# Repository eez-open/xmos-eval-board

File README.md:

### Ownership and License

The contributors are listed in CONTRIB.TXT. This project uses the TAPR v1.0 license, see LICENSE.TXT.
EEZ _xmos-eval-board_ uses the [C4.1 (Collective Code Construction Contract)](http://rfc.zeromq.org/spec:22) process for contributions.
To report an issue, use the [issue tracker](https://github.com/eez-open/xmos-eval-board/issues).

### Overview

This project is an attempt to learn more about [XMOS xCORE-200](http://www.xmos.com/products/silicon/xcore-200) multicore microcontroller XE216-512-TQ128 by making evaluation board that would be used as a prototype or building block in some future DIY open source Test & Measurement (T&M) projects.
Selected MCU has 16 _logical_ cores divided between two hardware cores (_tiles_)and include USB 2.0 and [RGMII](https://en.wikipedia.org/wiki/Media-independent_interface) for Gigabit Ethernet. It has the highest pin count that comes in easy to mounting package (not BGA).
The evaluation board is based on XMOS evaluation boards and a couple of so-called _sliceCARDs_.

Evaluation board features:

- PCB dimension: 100 x 85 mm
- Power supply: 12 Vdc with on board regulators for 1 V, 3.3 V (sequenced) and 5 V (for USB host)
- XSYS 20-pin IDC connector for JTAG and real-time debugging (via 2-wire _xlink0_) with ESD protection
- USB AB-mini 5-pin plug with ESD protection (hopefully can be used for [OTG](https://en.wikipedia.org/wiki/USB_On-The-Go) operation)
- Support for RGB 4.3" LCD TFT (40-pin FFC 0.5 mm), 16-bit color space supported
- LCD WLED power supply with brightness control (PWM)
- Resistive touch screen controller (SPI)
- QSPI Flash memory
- 10-pin IDC connector for direct access to Flash memory
- 16-bit I/O port expander with 2 opto-isolated input, 2 opto-isolated outputs, 3 on-board LEDs, 3 TVS protected inputs
- Real time clock (SPI) with supercap backup (Vbat)
- EEPROM (SPI)
- SDRAM (multiplexed address and data bus)
- 20-pin FFC 0.5 mm socket for Riverdi LCD TFT displays (SPI, Audio out)
- Micro SD Card socket (SPI)
- 10/100 Mbit Ethernet PHY with RJ-45 socket
- Low-power audio amplifier
- 10-pin header for cheap W5500 Ethernet module (SPI)
- Reset switch

For MCU pin mapping check _[Portmap for EEZ evaluation board](XE216-512-TQ128_portmap_for_EEZ_evaluation_board_r1B4.pdf)_

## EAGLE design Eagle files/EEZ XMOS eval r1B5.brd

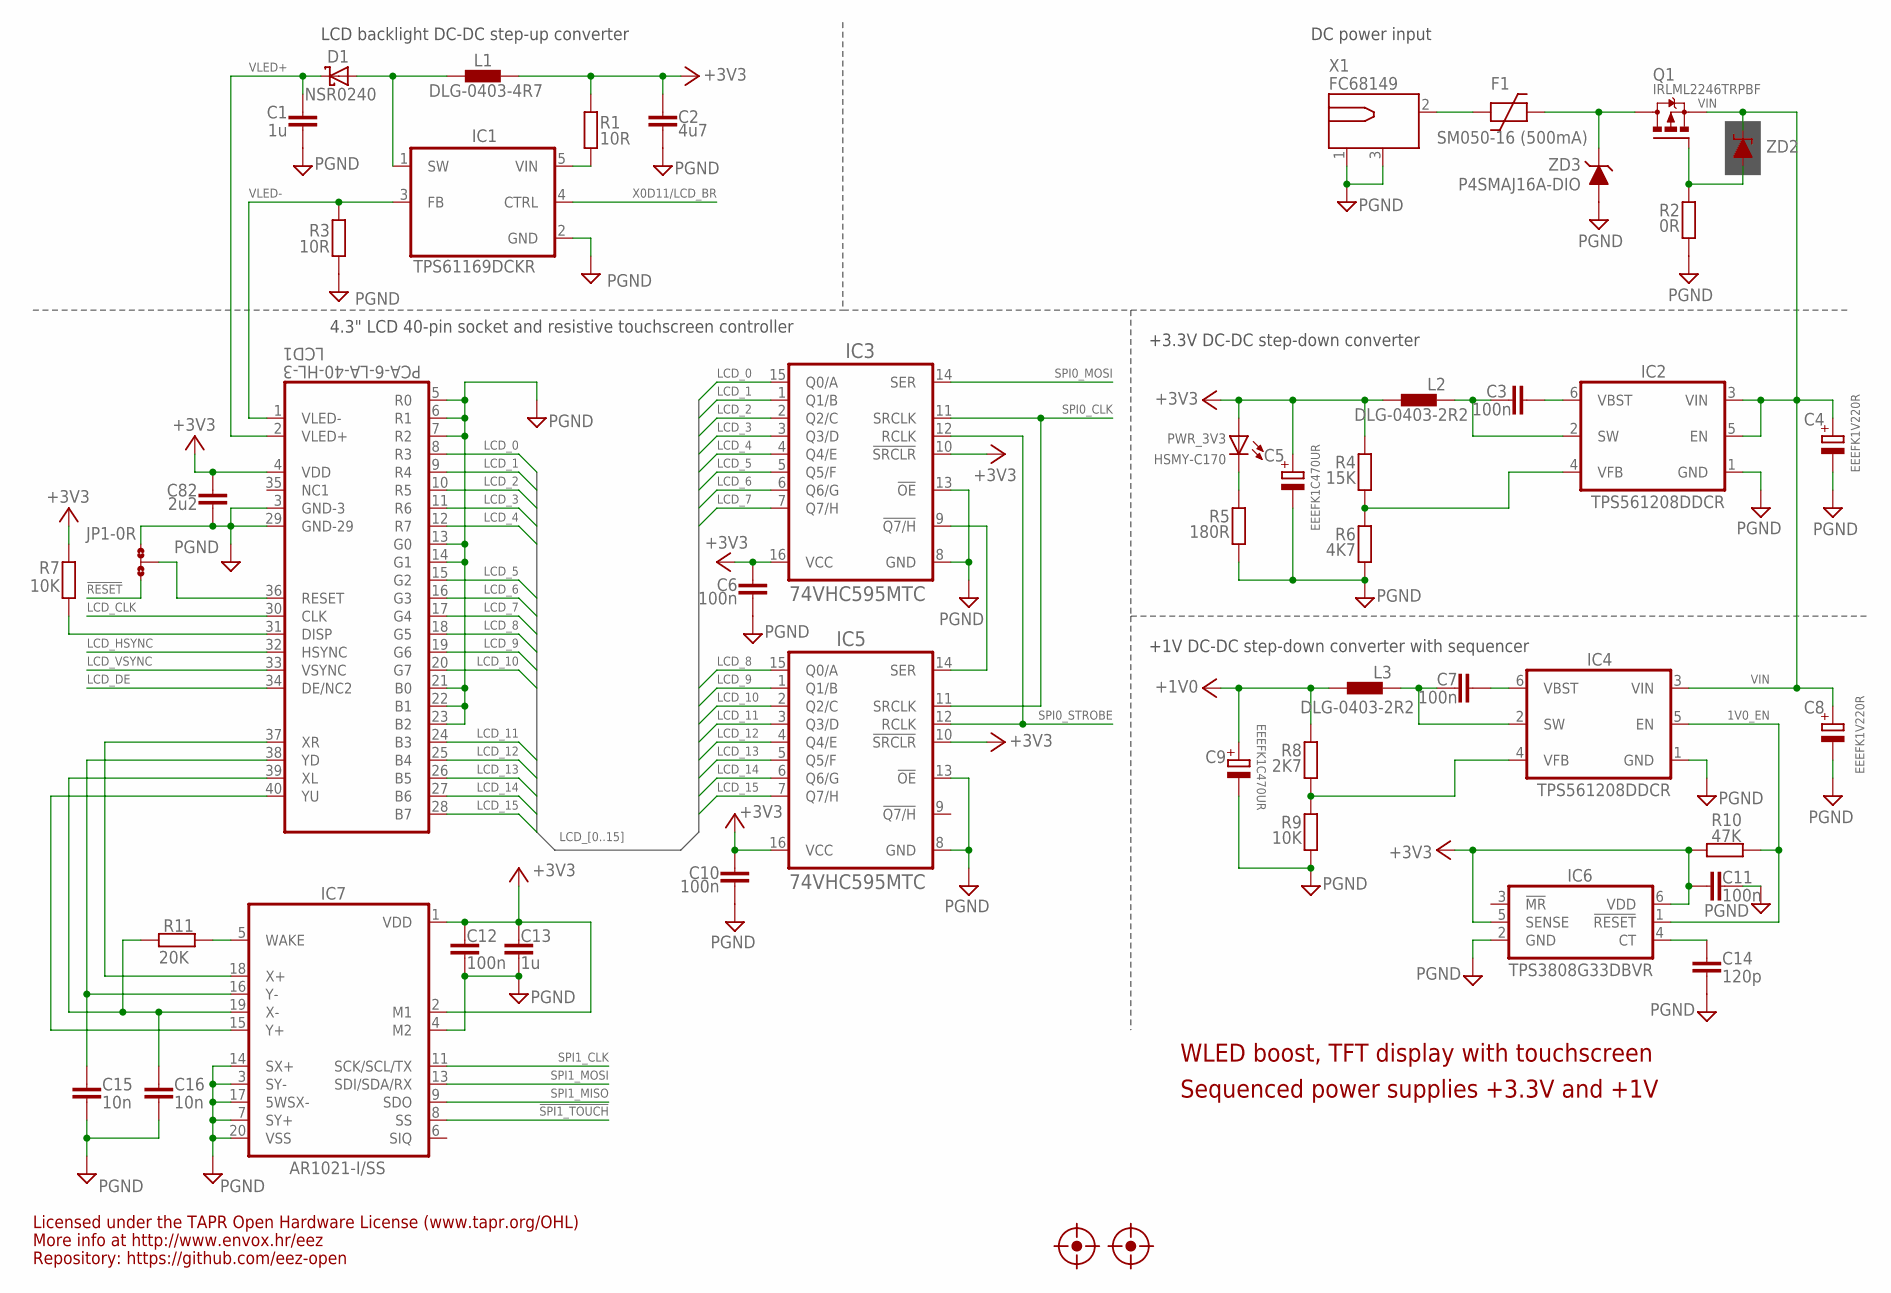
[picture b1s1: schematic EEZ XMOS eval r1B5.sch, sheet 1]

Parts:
C1, C13: 1u; C0805
C2: 4u7; C1206
C3, C6, C7, C10, C11, C12: 100n; C0603
C4: EEEFK1V220R; CAPAE530X610N
C5, C9: EEEFK1C470UR; CAPAE530X610N; TOLERANCE ±20 %; VOLTAGERATING 35V; MPN EEE-FK1V100R
C8: EEEFK1V220R; CAPAE530X610N; TOLERANCE ±20 %; VOLTAGERATING 35V; MPN EEE-FK1V100R
C14: 120p; C0805
C15, C16: 10n; C0805
C82: 2u2; C0805
D1: NSR0240; SOD123
F1: SM050-16 (500mA); F1210
FM1, FM2: FIDUCIAL_2; FIDUCIAL_DUAL
IC1: TPS61169DCKR; DCK0005A_N
IC2, IC4: TPS561208DDCR; DBV6
IC3, IC5: 74VHC595MTC; PW(R-PDSO-G16)
IC6: TPS3808G33DBVR; DBV6
IC7: AR1021-I/SS; SOP65P780X200-20N
JP1: 0R-JUMPA; A0R-JMP
L1: DLG-0403-4R7; DE0403
L2, L3: DLG-0403-2R2; DE0403
LCD1: PCA-6-LA-40-HL-3; FPC_40
PWR_3V3: HSMY-C170; LED_0805
Q1: IRLML2246TRPBF; SOT95P237X112-3N
R1, R3: 10R; R1206
R2: 0R; R0805
R4: 15K; R0805
R5: 180R; R0805
R6: 4K7; R0805
R7, R9: 10K; R0805
R8: 2K7; R0805
R10: 47K; R0805
R11: 20K; R0805
X1: FC68149; DC-21MM
ZD2: ZENER-DIODESOD323; SOD323-W
ZD3: P4SMAJ16A-DIO; DO214AC

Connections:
1V0_EN: IC4.5 (EN), IC6.1 (!RESET), R10.1
!RESET: JP1.1; also elsewhere on the board
!SPI1_TOUCH: IC7.8 (SS); also elsewhere on the board
+1V0: C9.1, L3.2, R8.2; also elsewhere on the board
+1V0_SW: C7.1, IC4.2 (SW), L3.1
+3V3: C2.1, C5.1, C6.2, C10.2, C11.2, C12.2, C13.2, C82.1, IC3.10 (!SRCLR), IC3.16 (VCC), IC5.10 (!SRCLR), IC5.16 (VCC), IC6.5 (SENSE), IC6.6 (VDD), IC7.1 (VDD), IC7.2 (M1), L1.1, L2.2, LCD1.4 (VDD), PWR_3V3.A, R1.1, R4.2, R7.2, R10.2; also elsewhere on the board
+3V3_SW: C3.1, IC2.2 (SW), L2.1
GND: C1.2, C2.2, C4.2, C5.2, C6.1, C8.2, C9.2, C10.1, C11.1, C12.1, C13.1, C14.2, C15.2, C16.2, C82.2, IC1.2 (GND), IC2.1 (GND), IC3.8 (GND), IC3.13 (!OE), IC4.1 (GND), IC5.8 (GND), IC5.13 (!OE), IC6.2 (GND), IC7.3 (SY-), IC7.4 (M2), IC7.7 (SY+), IC7.14 (SX+), IC7.17 (5WSX-), IC7.20 (VSS), JP1.3, LCD1.3 (GND-3), LCD1.5 (R0), LCD1.6 (R1), LCD1.7 (R2), LCD1.13 (G0), LCD1.14 (G1), LCD1.21 (B0), LCD1.22 (B1), LCD1.23 (B2), LCD1.29 (GND-29), R2.1, R3.2, R5.1, R6.1, R9.1, X1.1, X1.3, ZD3.A; also elsewhere on the board
LCD_0: IC3.15 (Q0/A), LCD1.8 (R3)
LCD_1: IC3.1 (Q1/B), LCD1.9 (R4)
LCD_2: IC3.2 (Q2/C), LCD1.10 (R5)
LCD_3: IC3.3 (Q3/D), LCD1.11 (R6)
LCD_4: IC3.4 (Q4/E), LCD1.12 (R7)
LCD_5: IC3.5 (Q5/F), LCD1.15 (G2)
LCD_6: IC3.6 (Q6/G), LCD1.16 (G3)
LCD_7: IC3.7 (Q7/H), LCD1.17 (G4)
LCD_8: IC5.15 (Q0/A), LCD1.18 (G5)
LCD_9: IC5.1 (Q1/B), LCD1.19 (G6)
LCD_10: IC5.2 (Q2/C), LCD1.20 (G7)
LCD_11: IC5.3 (Q3/D), LCD1.24 (B3)
LCD_12: IC5.4 (Q4/E), LCD1.25 (B4)
LCD_13: IC5.5 (Q5/F), LCD1.26 (B5)
LCD_14: IC5.6 (Q6/G), LCD1.27 (B6)
LCD_15: IC5.7 (Q7/H), LCD1.28 (B7)
LCD_CLK: LCD1.30 (CLK); also elsewhere on the board
LCD_DE: LCD1.34 (DE/NC2); also elsewhere on the board
LCD_HSYNC: LCD1.32 (HSYNC); also elsewhere on the board
LCD_VSYNC: LCD1.33 (VSYNC); also elsewhere on the board
unnamed: PWR_3V3.C, R5.2
unnamed: IC7.15 (Y+), LCD1.40 (YU)
unnamed: C16.1, IC7.19 (X-), LCD1.39 (XL), R11.2
unnamed: IC7.18 (X+), LCD1.37 (XR)
unnamed: Q1.1 (G), R2.2, ZD2.A
unnamed: IC7.5 (WAKE), R11.1
unnamed: F1.1, X1.2
unnamed: JP1.2, LCD1.36 (RESET)
unnamed: IC2.4 (VFB), R4.1, R6.2
unnamed: IC1.5 (VIN), R1.2
unnamed: C3.2, IC2.6 (VBST)
unnamed: IC3.9 (!Q7/H), IC5.14 (SER)
unnamed: IC4.4 (VFB), R8.1, R9.2
unnamed: C7.2, IC4.6 (VBST)
unnamed: C15.1, IC7.16 (Y-), LCD1.38 (YD)
unnamed: C14.1, IC6.4 (CT)
unnamed: LCD1.31 (DISP), R7.1
PMOS_D: F1.2, Q1.3 (D), ZD3.C
SPI0_CLK: IC3.11 (SRCLK), IC5.11 (SRCLK); also elsewhere on the board
SPI0_MOSI: IC3.14 (SER); also elsewhere on the board
SPI0_STROBE: IC3.12 (RCLK), IC5.12 (RCLK); also elsewhere on the board
SPI1_CLK: IC7.11 (SCK/SCL/TX); also elsewhere on the board
SPI1_MISO: IC7.9 (SDO); also elsewhere on the board
SPI1_MOSI: IC7.13 (SDI/SDA/RX); also elsewhere on the board
SW_WLED: D1.A, IC1.1 (SW), L1.2
VIN: C4.1, C8.1, IC2.3 (VIN), IC2.5 (EN), IC4.3 (VIN), Q1.2 (S), ZD2.C; also elsewhere on the board
VLED+: C1.1, D1.C, LCD1.2 (VLED+)
VLED-: IC1.3 (FB), LCD1.1 (VLED-), R3.1
X0D11/LCD_BR: IC1.4 (CTRL); also elsewhere on the board

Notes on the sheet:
Licensed under the TAPR Open Hardware License (www.tapr.org/OHL)
Repository: https://github.com/eez-open
More info at http://www.envox.hr/eez
Sequenced power supplies +3.3V and +1V
4.3" LCD 40-pin socket and resistive touchscreen controller
LCD backlight DC-DC step-up converter
WLED boost, TFT display with touchscreen
DC power input
+3.3V DC-DC step-down converter
+1V DC-DC step-down converter with sequencer

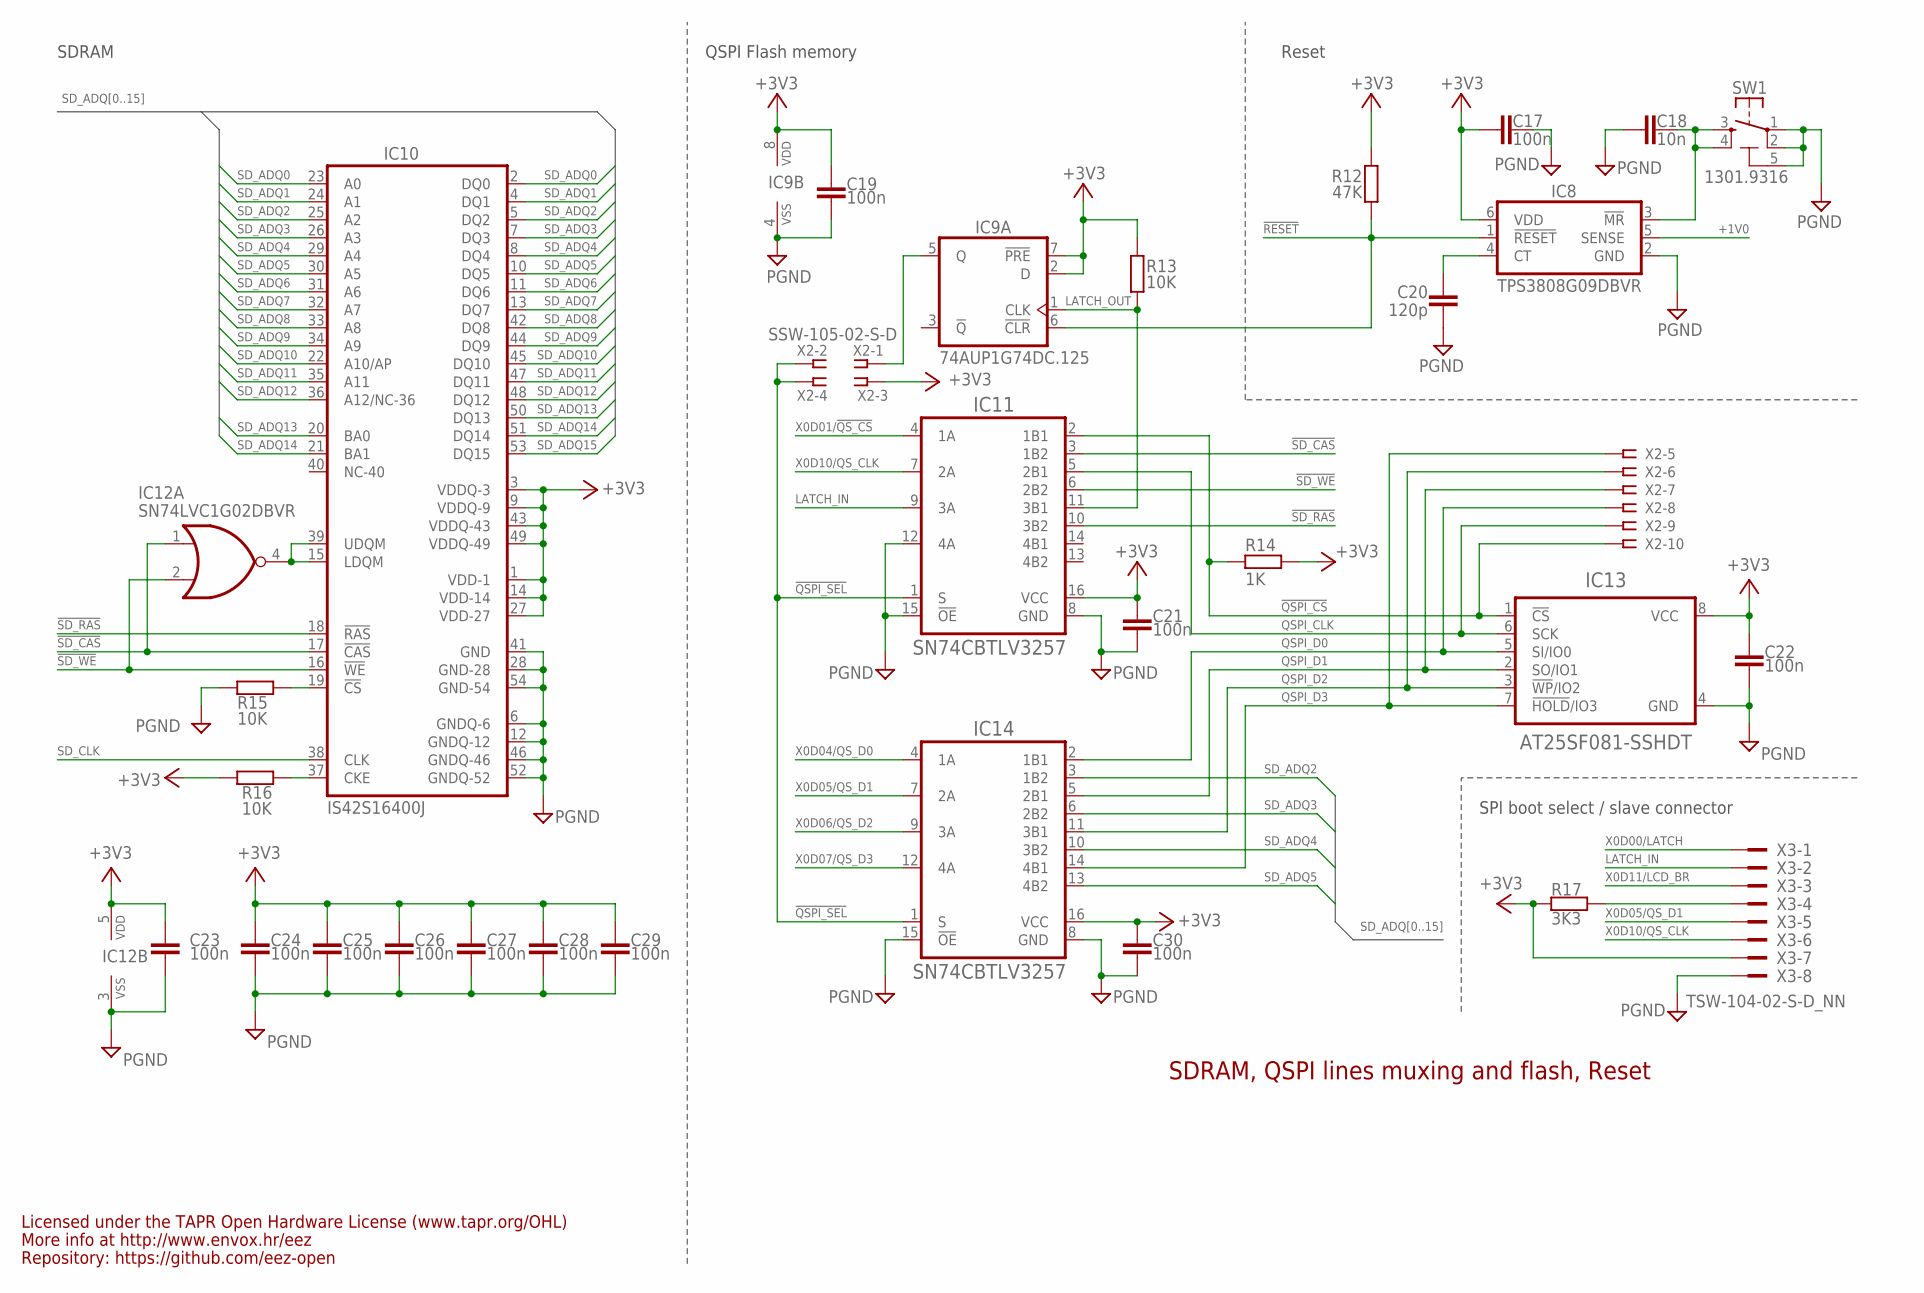
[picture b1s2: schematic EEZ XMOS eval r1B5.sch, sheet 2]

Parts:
C17, C19, C21, C22, C23, C24, C25, C26, C27, C28, C29, C30: 100n; C0603
C18: 10n; C0805
C20: 120p; C0805
IC8: TPS3808G09DBVR; DBV6; MANUFACTURER_PART_NUMBER tps3808g01_dbv_6
IC9: 74AUP1G74DC.125; DCU8
IC10: IS42S16400J; TSOPII-54
IC11, IC14: SN74CBTLV3257; PW(R-PDSO-G16)
IC12: SN74LVC1G02DBVR; DBV5
IC13: AT25SF081-SSHDT; SOIC127P600X175-8N
R12: 47K; R0805
R13, R15, R16: 10K; R0805
R14: 1K; R0805
R17: 3K3; R0805
SW1: 1301.9316; TACTM-6XN
X2: SSW-105-02-S-D
X3: TSW-104-02-S-D_NN; TSW-104-02-S-D-NONUM

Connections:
!QSPI_CS: IC11.2 (1B1), IC13.1 (!CS), R14.2, X2.10
!QSPI_SEL: IC11.1 (S), IC14.1 (S), X2.2, X2.4
!RESET: IC8.1 (!RESET), IC9.6 (!CLR), R12.2; also elsewhere on the board
!SD_CAS: IC10.17 (!CAS), IC11.3 (1B2), IC12.1 (A)
!SD_RAS: IC10.18 (!RAS), IC11.10 (3B2)
!SD_WE: IC10.16 (!WE), IC11.6 (2B2), IC12.2 (B)
+1V0: IC8.5 (SENSE); also elsewhere on the board
+3V3: C17.1, C19.1, C21.1, C22.1, C23.1, C24.1, C25.1, C26.1, C27.1, C28.1, C29.1, C30.1, IC8.6 (VDD), IC9.2 (D), IC9.7 (!PRE), IC9.8 (VDD), IC10.1 (VDD-1), IC10.3 (VDDQ-3), IC10.9 (VDDQ-9), IC10.14 (VDD-14), IC10.27 (VDD-27), IC10.43 (VDDQ-43), IC10.49 (VDDQ-49), IC11.16 (VCC), IC12.5 (VDD), IC13.8 (VCC), IC14.16 (VCC), R12.1, R13.1, R14.1, R16.2, R17.2, X2.3, X3.7; also elsewhere on the board
GND: C17.2, C18.1, C19.2, C20.2, C21.2, C22.2, C23.2, C24.2, C25.2, C26.2, C27.2, C28.2, C29.2, C30.2, IC8.2 (GND), IC9.4 (VSS), IC10.6 (GNDQ-6), IC10.12 (GNDQ-12), IC10.28 (GND-28), IC10.41 (GND), IC10.46 (GNDQ-46), IC10.52 (GNDQ-52), IC10.54 (GND-54), IC11.8 (GND), IC11.12 (4A), IC11.15 (!OE), IC12.3 (VSS), IC13.4 (GND), IC14.8 (GND), IC14.15 (!OE), R15.2, SW1.1, SW1.2, SW1.5 (5-GND), X3.8; also elsewhere on the board
LATCH_IN: IC11.9 (3A), X3.2
LATCH_OUT: IC9.1 (CLK), IC11.11 (3B1), R13.2
unnamed: R17.1, X3.4
unnamed: IC10.19 (!CS), R15.1
unnamed: IC10.15 (LDQM), IC10.39 (UDQM), IC12.4 (Y)
unnamed: IC10.37 (CKE), R16.1
unnamed: C20.1, IC8.4 (CT)
unnamed: C18.2, IC8.3 (!MR), SW1.3, SW1.4
unnamed: IC9.5 (Q), X2.1
QSPI_CLK: IC11.5 (2B1), IC13.6 (SCK), X2.9
QSPI_D0: IC13.5 (SI/IO0), IC14.2 (1B1), X2.8
QSPI_D1: IC13.2 (SO/IO1), IC14.5 (2B1), X2.7
QSPI_D2: IC13.3 (!WP!/IO2), IC14.11 (3B1), X2.6
QSPI_D3: IC13.7 (!HOLD!/IO3), IC14.14 (4B1), X2.5
SD_ADQ0: IC10.2 (DQ0), IC10.23 (A0); also elsewhere on the board
SD_ADQ1: IC10.4 (DQ1), IC10.24 (A1); also elsewhere on the board
SD_ADQ2: IC10.5 (DQ2), IC10.25 (A2), IC14.3 (1B2)
SD_ADQ3: IC10.7 (DQ3), IC10.26 (A3), IC14.6 (2B2)
SD_ADQ4: IC10.8 (DQ4), IC10.29 (A4), IC14.10 (3B2)
SD_ADQ5: IC10.10 (DQ5), IC10.30 (A5), IC14.13 (4B2)
SD_ADQ6: IC10.11 (DQ6), IC10.31 (A6); also elsewhere on the board
SD_ADQ7: IC10.13 (DQ7), IC10.32 (A7); also elsewhere on the board
SD_ADQ8: IC10.33 (A8), IC10.42 (DQ8); also elsewhere on the board
SD_ADQ9: IC10.34 (A9), IC10.44 (DQ9); also elsewhere on the board
SD_ADQ10: IC10.22 (A10/AP), IC10.45 (DQ10); also elsewhere on the board
SD_ADQ11: IC10.35 (A11), IC10.47 (DQ11); also elsewhere on the board
SD_ADQ12: IC10.36 (A12/NC-36), IC10.48 (DQ12); also elsewhere on the board
SD_ADQ13: IC10.20 (BA0), IC10.50 (DQ13); also elsewhere on the board
SD_ADQ14: IC10.21 (BA1), IC10.51 (DQ14); also elsewhere on the board
SD_ADQ15: IC10.53 (DQ15); also elsewhere on the board
SD_CLK: IC10.38 (CLK); also elsewhere on the board
X0D00/LATCH: X3.1; also elsewhere on the board
X0D01/!QS_CS: IC11.4 (1A); also elsewhere on the board
X0D04/QS_D0: IC14.4 (1A); also elsewhere on the board
X0D05/QS_D1: IC14.7 (2A), X3.5; also elsewhere on the board
X0D06/QS_D2: IC14.9 (3A); also elsewhere on the board
X0D07/QS_D3: IC14.12 (4A); also elsewhere on the board
X0D10/QS_CLK: IC11.7 (2A), X3.6; also elsewhere on the board
X0D11/LCD_BR: X3.3; also elsewhere on the board

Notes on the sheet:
Licensed under the TAPR Open Hardware License (www.tapr.org/OHL)
Repository: https://github.com/eez-open
More info at http://www.envox.hr/eez
SDRAM, QSPI lines muxing and flash, Reset
QSPI Flash memory
SDRAM
Reset
SPI boot select / slave connector

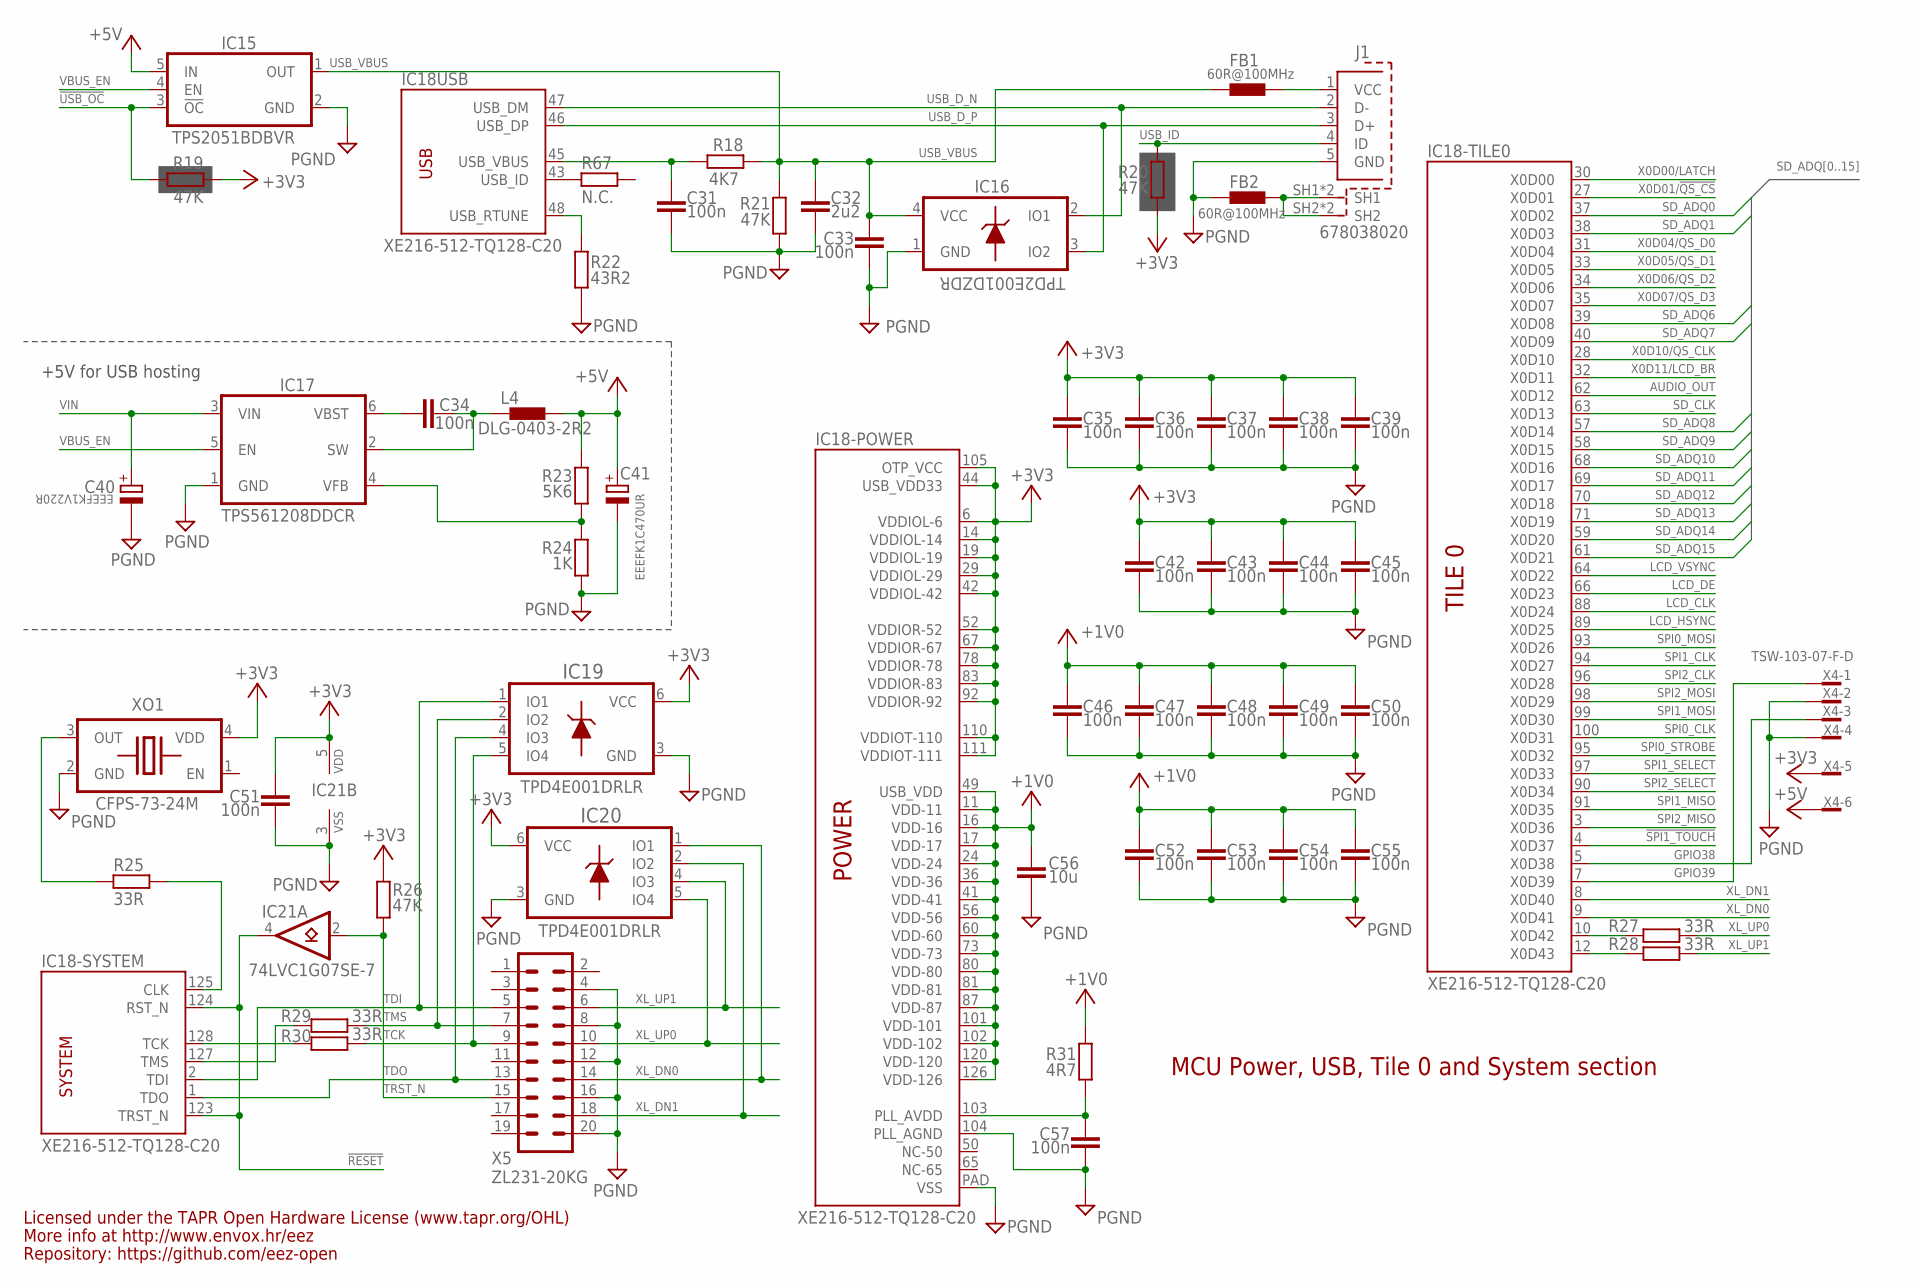
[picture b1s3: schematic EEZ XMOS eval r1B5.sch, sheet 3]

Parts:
C31, C33, C34, C35, C36, C37, C38, C39, C42, C43, C44, C45, C46, C47, C48, C49, C50, C51, C52, C53, C54, C55, C57: 100n; C0603
C32: 2u2; C0805
C40: EEEFK1V220R; CAPAE530X610N
C41: EEEFK1C470UR; CAPAE530X610N; TOLERANCE ±20 %; VOLTAGERATING 35V; MPN EEE-FK1V100R
C56: 10u; C1210
FB1, FB2: 60R@100MHz; BEAD0603
IC15: TPS2051BDBVR; DBV5
IC16: TPD2E001DZDR; SOP192P292X122-4N
IC17: TPS561208DDCR; DBV6
IC18: XE216-512-TQ128-C20; TQ128
IC19, IC20: TPD4E001DRLR; DRL6
IC21: 74LVC1G07SE-7; DCK5
J1: 678038020
L4: DLG-0403-2R2; DE0403
R18: 4K7; R0805
R19, R20, R21, R26: 47K; R0805
R22: 43R2; R0805
R23: 5K6; R0805
R24: 1K; R0805
R25, R27, R28, R29, R30: 33R; R0603
R31: 4R7; R0805
R67: N.C.; R0805
X4: TSW-103-07-F-D
X5: ZL231-20KG; ML20L
XO1: CFPS-73-24M; 12SMX(C)

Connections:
!RESET: IC18.123 (TRST_N), IC18.124 (RST_N), IC21.4 (Y); also elsewhere on the board
!SPI1_TOUCH: IC18.4 (X0D37); also elsewhere on the board
!USB_OC: IC15.3 (!OC), R19.1; also elsewhere on the board
+1V0: C46.1, C47.1, C48.1, C49.1, C50.1, C52.1, C53.1, C54.1, C55.1, C56.1, IC18.11 (VDD-11), IC18.16 (VDD-16), IC18.17 (VDD-17), IC18.24 (VDD-24), IC18.36 (VDD-36), IC18.41 (VDD-41), IC18.49 (USB_VDD), IC18.56 (VDD-56), IC18.60 (VDD-60), IC18.73 (VDD-73), IC18.80 (VDD-80), IC18.81 (VDD-81), IC18.87 (VDD-87), IC18.101 (VDD-101), IC18.102 (VDD-102), IC18.120 (VDD-120), IC18.126 (VDD-126), R31.1; also elsewhere on the board
+3V3: C35.1, C36.1, C37.1, C38.1, C39.1, C42.1, C43.1, C44.1, C45.1, C51.1, IC18.6 (VDDIOL-6), IC18.14 (VDDIOL-14), IC18.19 (VDDIOL-19), IC18.29 (VDDIOL-29), IC18.42 (VDDIOL-42), IC18.44 (USB_VDD33), IC18.52 (VDDIOR-52), IC18.67 (VDDIOR-67), IC18.78 (VDDIOR-78), IC18.83 (VDDIOR-83), IC18.92 (VDDIOR-92), IC18.105 (OTP_VCC), IC18.110 (VDDIOT-110), IC18.111 (VDDIOT-111), IC19.6 (VCC), IC20.6 (VCC), IC21.5 (VDD), R19.2, R20.1, R26.1, X4.5, XO1.4 (VDD); also elsewhere on the board
+5V: C41.1, IC15.5 (IN), L4.2, R23.2, X4.6
+5V_SW: C34.1, IC17.2 (SW), L4.1
AUDIO_OUT: IC18.62 (X0D12); also elsewhere on the board
GND: C31.2, C32.2, C33.1, C35.2, C36.2, C37.2, C38.2, C39.2, C40.2, C41.2, C42.2, C43.2, C44.2, C45.2, C46.2, C47.2, C48.2, C49.2, C50.2, C51.2, C52.2, C53.2, C54.2, C55.2, C56.2, C57.2, FB2.P$1 (1), IC15.2 (GND), IC16.1 (GND), IC17.1 (GND), IC18.104 (PLL_AGND), IC18.PAD (VSS), IC19.3 (GND), IC20.3 (GND), IC21.3 (VSS), J1.5 (GND), R21.2, R22.2, R24.1, X4.2, X4.4, X5.4, X5.8, X5.12, X5.16, X5.20, XO1.2 (GND); also elsewhere on the board
GPIO38: IC18.5 (X0D38), X4.3
GPIO39: IC18.7 (X0D39), X4.1
LCD_CLK: IC18.88 (X0D24); also elsewhere on the board
LCD_DE: IC18.66 (X0D23); also elsewhere on the board
LCD_HSYNC: IC18.89 (X0D25); also elsewhere on the board
LCD_VSYNC: IC18.64 (X0D22); also elsewhere on the board
unnamed: IC18.10 (X0D42), R27.1
unnamed: IC18.12 (X0D43), R28.1
unnamed: IC18.125 (CLK), R25.2
unnamed: IC18.43 (USB_ID), R67.1
unnamed: C57.1, IC18.103 (PLL_AVDD), R31.2
unnamed: FB2.P$2 (2), J1.SH1, J1.SH1.1 (SH1), J1.SH2, J1.SH2.2 (SH2)
unnamed: IC18.48 (USB_RTUNE), R22.1
unnamed: C31.1, IC18.45 (USB_VBUS), R18.2
unnamed: IC18.127 (TMS), R29.1
unnamed: IC18.128 (TCK), R30.1
unnamed: IC17.4 (VFB), R23.1, R24.2
unnamed: FB1.P$2 (2), J1.1 (VCC)
unnamed: C34.2, IC17.6 (VBST)
unnamed: R25.1, XO1.3 (OUT)
SD_ADQ0: IC18.37 (X0D02); also elsewhere on the board
SD_ADQ1: IC18.38 (X0D03); also elsewhere on the board
SD_ADQ6: IC18.39 (X0D08); also elsewhere on the board
SD_ADQ7: IC18.40 (X0D09); also elsewhere on the board
SD_ADQ8: IC18.57 (X0D14); also elsewhere on the board
SD_ADQ9: IC18.58 (X0D15); also elsewhere on the board
SD_ADQ10: IC18.68 (X0D16); also elsewhere on the board
SD_ADQ11: IC18.69 (X0D17); also elsewhere on the board
SD_ADQ12: IC18.70 (X0D18); also elsewhere on the board
SD_ADQ13: IC18.71 (X0D19); also elsewhere on the board
SD_ADQ14: IC18.59 (X0D20); also elsewhere on the board
SD_ADQ15: IC18.61 (X0D21); also elsewhere on the board
SD_CLK: IC18.63 (X0D13); also elsewhere on the board
SPI0_CLK: IC18.100 (X0D31); also elsewhere on the board
SPI0_MOSI: IC18.93 (X0D26); also elsewhere on the board
SPI0_STROBE: IC18.95 (X0D32); also elsewhere on the board
SPI1_CLK: IC18.94 (X0D27); also elsewhere on the board
SPI1_MISO: IC18.91 (X0D35); also elsewhere on the board
SPI1_MOSI: IC18.99 (X0D30); also elsewhere on the board
SPI1_SELECT: IC18.97 (X0D33); also elsewhere on the board
SPI2_CLK: IC18.96 (X0D28); also elsewhere on the board
SPI2_MISO: IC18.3 (X0D36); also elsewhere on the board
SPI2_MOSI: IC18.98 (X0D29); also elsewhere on the board
SPI2_SELECT: IC18.90 (X0D34); also elsewhere on the board
TCK: IC19.5 (IO4), R30.2, X5.9
TDI: IC18.2 (TDI), IC19.1 (IO1), X5.5
TDO: IC18.1 (TDO), IC19.4 (IO3), X5.13
TMS: IC19.2 (IO2), R29.2, X5.7
TRST_N: IC21.2 (A), R26.2, X5.15
USB_D_N: IC16.2 (IO1), IC18.47 (USB_DM), J1.2 (D-)
USB_D_P: IC16.3 (IO2), IC18.46 (USB_DP), J1.3 (D+)
USB_ID: J1.4 (ID), R20.2; also elsewhere on the board
USB_VBUS: C32.1, C33.2, FB1.P$1 (1), IC15.1 (OUT), IC16.4 (VCC), R18.1, R21.1
VBUS_EN: IC15.4 (EN), IC17.5 (EN); also elsewhere on the board
VIN: C40.1, IC17.3 (VIN); also elsewhere on the board
X0D00/LATCH: IC18.30 (X0D00); also elsewhere on the board
X0D01/!QS_CS: IC18.27 (X0D01); also elsewhere on the board
X0D04/QS_D0: IC18.31 (X0D04); also elsewhere on the board
X0D05/QS_D1: IC18.33 (X0D05); also elsewhere on the board
X0D06/QS_D2: IC18.34 (X0D06); also elsewhere on the board
X0D07/QS_D3: IC18.35 (X0D07); also elsewhere on the board
X0D10/QS_CLK: IC18.28 (X0D10); also elsewhere on the board
X0D11/LCD_BR: IC18.32 (X0D11); also elsewhere on the board
XL_DN0: IC18.9 (X0D41), IC20.1 (IO1), X5.14
XL_DN1: IC18.8 (X0D40), IC20.2 (IO2), X5.18
XL_UP0: IC20.5 (IO4), R27.2, X5.10
XL_UP1: IC20.4 (IO3), R28.2, X5.6

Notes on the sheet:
Licensed under the TAPR Open Hardware License (www.tapr.org/OHL)
Repository: https://github.com/eez-open
More info at http://www.envox.hr/eez
MCU Power, USB, Tile 0 and System section
+5V for USB hosting

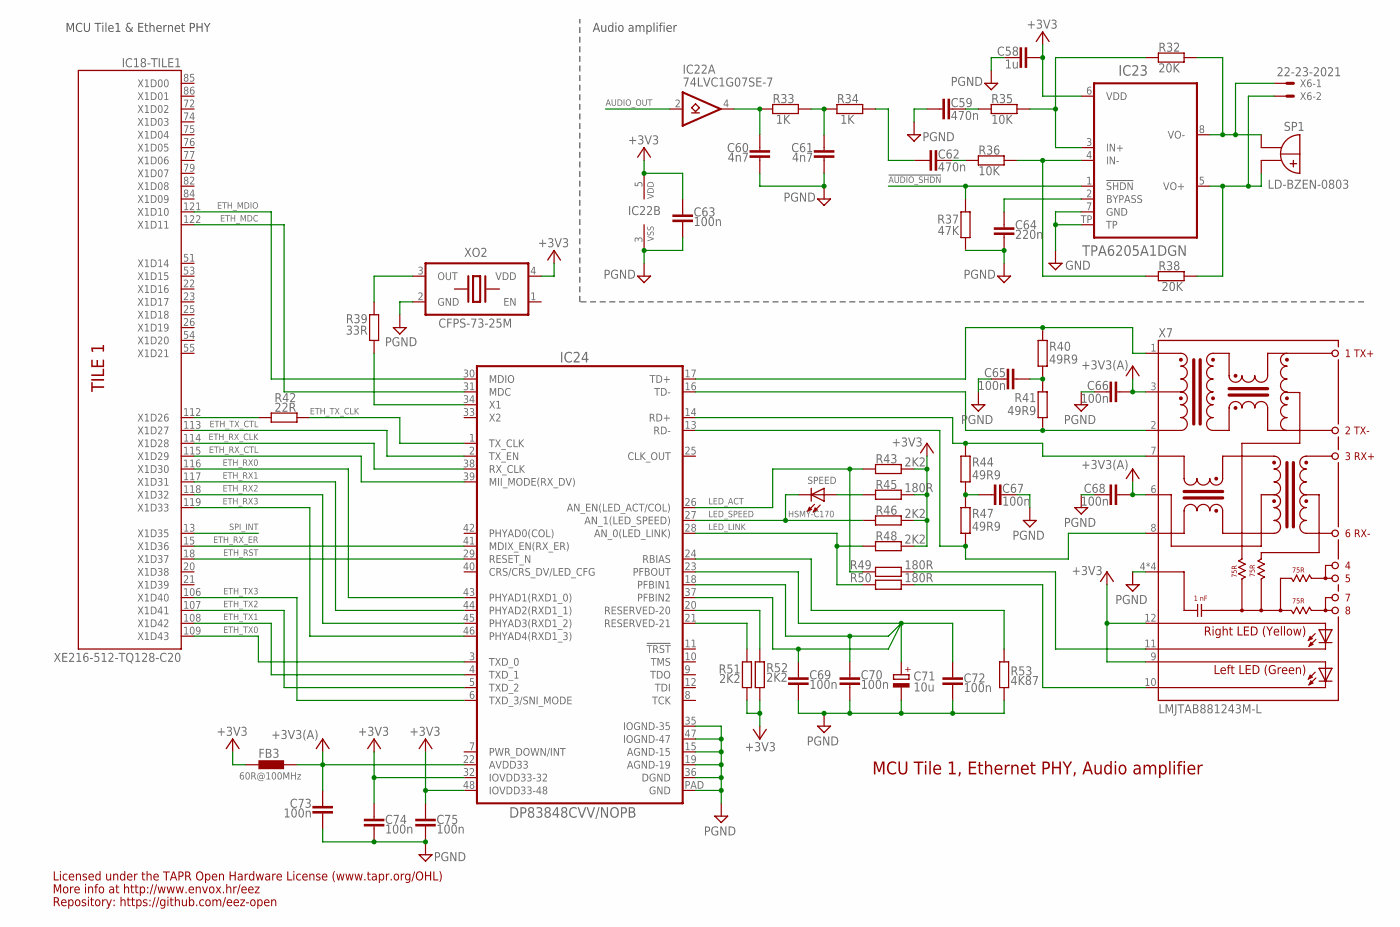
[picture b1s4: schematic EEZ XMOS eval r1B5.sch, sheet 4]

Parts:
C58: 1u; C0805
C59, C62: 470n; C0805
C60, C61: 4n7; C0805
C63, C65, C66, C67, C68, C69, C70, C72, C73, C74, C75: 100n; C0603
C64: 220n; C0805
C71: 10u; EC1206
FB3: 60R@100MHz; BEAD0603
IC18: XE216-512-TQ128-C20; TQ128
IC22: 74LVC1G07SE-7; DCK5
IC23: TPA6205A1DGN; SOP65P490X110-9N
IC24: DP83848CVV/NOPB; PT48+PAD
R32, R38: 20K; R0805
R33, R34: 1K; R0805
R35, R36: 10K; R0805
R37: 47K; R0805
R39: 33R; R0603
R40, R41, R44, R47: 49R9; R0805
R42: 22R; R0805
R43, R46, R48, R51, R52: 2K2; R0805
R45, R49, R50: 180R; R0805
R53: 4K87; R0603
SP1: LD-BZEN-0803
SPEED: HSMY-C170; LED_0805
X6: 22-23-2021; MPN 22-23-2021
X7: LMJTAB881243M-L; RJ45-TRAFO-LED
XO2: CFPS-73-25M; 12SMX(C)

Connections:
!AUDIO_SHDN: IC23.1 (!SHDN), R37.1; also elsewhere on the board
+3V3: C58.2, C63.2, C74.1, C75.1, FB3.P$1 (1), IC22.5 (VDD), IC23.6 (VDD), IC24.32 (IOVDD33-32), IC24.48 (IOVDD33-48), R43.1, R45.1, R46.1, R48.1, R51.1, R52.1, X7.9 (GREEN-A), X7.12 (YELLOW_A), XO2.4 (VDD); also elsewhere on the board
+3V3(A): C66.2, C68.2, C73.1, FB3.P$2 (2), IC24.22 (AVDD33), X7.3 (CT), X7.6 (CR)
AUDIO_OUT: IC22.2 (A); also elsewhere on the board
ETH_MDC: IC18.122 (X1D11), IC24.31 (MDC)
ETH_MDIO: IC18.121 (X1D10), IC24.30 (MDIO)
ETH_RST: IC18.18 (X1D37), IC24.29 (RESET_N); also elsewhere on the board
ETH_RX0: IC18.116 (X1D30), IC24.43 (PHYAD1(RXD1_0))
ETH_RX1: IC18.117 (X1D31), IC24.44 (PHYAD2(RXD1_1))
ETH_RX2: IC18.118 (X1D32), IC24.45 (PHYAD3(RXD1_2))
ETH_RX3: IC18.119 (X1D33), IC24.46 (PHYAD4(RXD1_3))
ETH_RX_CLK: IC18.114 (X1D28), IC24.38 (RX_CLK)
ETH_RX_CTL: IC18.115 (X1D29), IC24.39 (MII_MODE(RX_DV))
ETH_RX_ER: IC18.15 (X1D36), IC24.41 (MDIX_EN(RX_ER))
ETH_TX0: IC18.109 (X1D43), IC24.3 (TXD_0)
ETH_TX1: IC18.108 (X1D42), IC24.4 (TXD_1)
ETH_TX2: IC18.107 (X1D41), IC24.5 (TXD_2)
ETH_TX3: IC18.106 (X1D40), IC24.6 (TXD_3/SNI_MODE)
ETH_TX_CLK: IC24.1 (TX_CLK), R42.2
ETH_TX_CTL: IC18.113 (X1D27), IC24.2 (TX_EN)
GND: C58.1, C59.2, C60.2, C61.2, C63.1, C64.1, C65.2, C66.1, C67.2, C68.1, C69.2, C70.2, C71.-, C72.2, C73.2, C74.2, C75.2, IC22.3 (VSS), IC23.7 (GND), IC23.TP, IC24.15 (AGND-15), IC24.19 (AGND-19), IC24.35 (IOGND-35), IC24.36 (DGND), IC24.47 (IOGND-47), IC24.PAD (GND), R37.2, R53.1, X7.4 (SH), X7.5 (SH), X7.SH1 (SH), X7.SH2 (SH), XO2.2 (GND); also elsewhere on the board
LED_ACT: IC24.26 (AN_EN(LED_ACT/COL)), R43.2, R49.2
LED_LINK: IC24.28 (AN_0(LED_LINK)), R48.2, R50.2
LED_SPEED: IC24.27 (AN_1(LED_SPEED)), R46.2, SPEED.C
unnamed: IC18.112 (X1D26), R42.1
unnamed: IC24.34 (X1), R39.2
unnamed: R49.1, X7.11 (YELLOW-C)
unnamed: R50.1, X7.10 (GREEN-C)
unnamed: R39.1, XO2.3 (OUT)
unnamed: IC23.5 (VO+), R38.1, SP1.+, X6.2
unnamed: IC24.24 (RBIAS), R53.2
unnamed: IC24.21 (RESERVED-21), R51.2
unnamed: IC24.20 (RESERVED-20), R52.2
unnamed: R45.2, SPEED.A
unnamed: C67.1, R44.1, R47.2
unnamed: C65.1, R40.1, R41.2
unnamed: IC23.8 (VO-), R32.1, SP1.-, X6.1
unnamed: IC23.4 (IN-), R36.1, R38.2
unnamed: IC23.3 (IN+), R32.2, R35.1
unnamed: C59.1, R35.2
unnamed: C64.2, IC23.2 (BYPASS)
unnamed: C62.1, R36.2
unnamed: C62.2, R34.1
unnamed: C61.1, R33.1, R34.2
unnamed: C60.1, IC22.4 (Y), R33.2
PFBOUT: C69.1, C70.1, C71.+, C72.1, IC24.18 (PFBIN1), IC24.23 (PFBOUT), IC24.37 (PFBIN2)
RD+: IC24.14 (RD+), R44.2, X7.7 (RD+)
RD-: IC24.13 (RD-), R47.1, X7.8 (RD-)
SPI_INT: IC18.13 (X1D35); also elsewhere on the board
TD+: IC24.17 (TD+), R40.2, X7.1 (TD+)
TD-: IC24.16 (TD-), R41.1, X7.2 (TD-)

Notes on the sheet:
Licensed under the TAPR Open Hardware License (www.tapr.org/OHL)
Repository: https://github.com/eez-open
More info at http://www.envox.hr/eez
MCU Tile 1, Ethernet PHY, Audio amplifier
Audio amplifier
MCU Tile1 & Ethernet PHY
